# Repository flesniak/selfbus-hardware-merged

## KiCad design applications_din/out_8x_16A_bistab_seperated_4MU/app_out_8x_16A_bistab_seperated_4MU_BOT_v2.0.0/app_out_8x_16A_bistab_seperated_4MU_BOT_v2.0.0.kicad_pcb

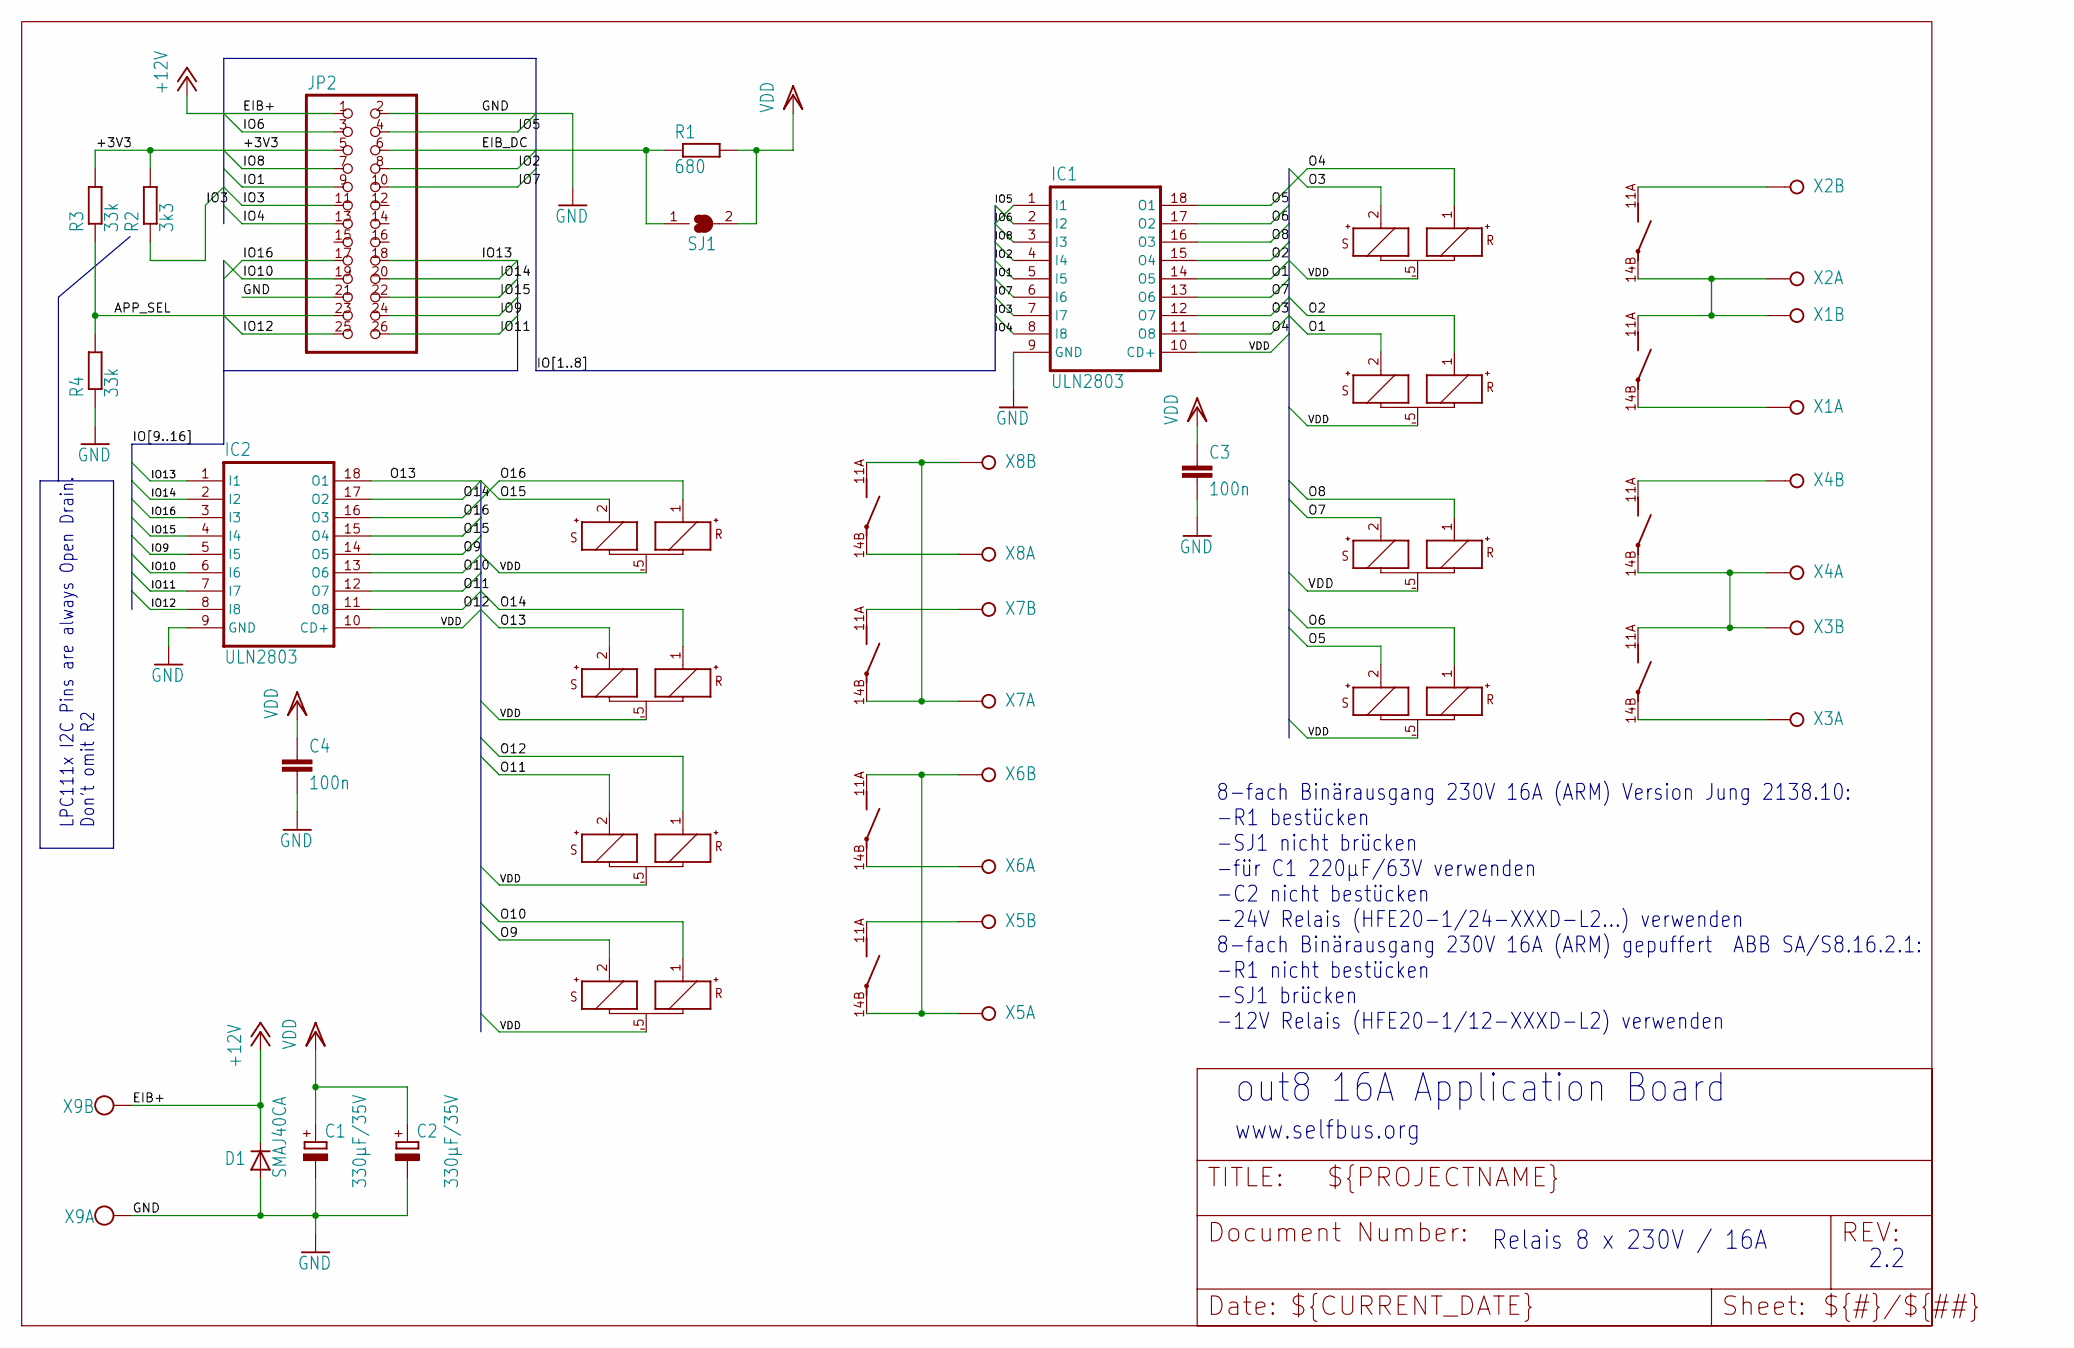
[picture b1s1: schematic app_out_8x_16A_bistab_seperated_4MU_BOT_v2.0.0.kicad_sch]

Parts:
C1, C2: 330µF/35V; E3,5-8
C3, C4: 100n; C1206
D1: SMAJ40CA; SMB
IC1, IC2: ULN2803; SO18W
JP2: A; 2X13SMD
K1, K2, K3, K4, K5, K6, K7, K8: HFE20-1-024-1HD504; HFE20-3-504
R1: 680; M1206
R2: 3k3; M1206
R3, R4: 33k; M1206
SJ1: A; SolderJumper-2_P1.3mm_Open_Pad1.0x1.5mm
X1, X2, X3, X4, X5, X6, X7, X8: W237-02P; W237-132
X9: W237-102; W237-132

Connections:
+12V: D1.1 (C), JP2.1, X9.2 (KL)
/+3V3: JP2.5, R2.2, R3.2
/APP_SEL: JP2.23, R3.1, R4.2
/EIB_DC: JP2.6, R1.1, SJ1.1
/IO1: IC1.5 (I5), JP2.9
/IO2: IC1.4 (I4), JP2.8
/IO3: IC1.7 (I7), JP2.11, R2.1
/IO4: IC1.8 (I8), JP2.13
/IO5: IC1.1 (I1), JP2.4
/IO6: IC1.2 (I2), JP2.3
/IO7: IC1.6 (I6), JP2.10
/IO8: IC1.3 (I3), JP2.7
/IO9: IC2.5 (I5), JP2.24
/IO10: IC2.6 (I6), JP2.19
/IO11: IC2.7 (I7), JP2.26
/IO12: IC2.8 (I8), JP2.25
/IO13: IC2.1 (I1), JP2.18
/IO14: IC2.2 (I2), JP2.20
/IO15: IC2.4 (I4), JP2.22
/IO16: IC2.3 (I3), JP2.17
/O1: IC1.14 (O5), K1.2 (S+)
/O2: IC1.15 (O4), K1.1 (R+)
/O3: IC1.12 (O7), K2.2 (S+)
/O4: IC1.11 (O8), K2.1 (R+)
/O5: IC1.18 (O1), K3.2 (S+)
/O6: IC1.17 (O2), K3.1 (R+)
/O7: IC1.13 (O6), K4.2 (S+)
/O8: IC1.16 (O3), K4.1 (R+)
/O9: IC2.14 (O5), K5.2 (S+)
/O10: IC2.13 (O6), K5.1 (R+)
/O11: IC2.12 (O7), K6.2 (S+)
/O12: IC2.11 (O8), K6.1 (R+)
/O13: IC2.18 (O1), K7.2 (S+)
/O14: IC2.17 (O2), K7.1 (R+)
/O15: IC2.15 (O4), K8.2 (S+)
/O16: IC2.16 (O3), K8.1 (R+)
GND: C1.-, C2.-, C3.2, C4.2, D1.2 (A), IC1.9 (GND), IC2.9 (GND), JP2.2, JP2.21, R4.1, X9.1 (KL)
unnamed: K1.14B (PA), X1.1 (KL)
unnamed: K1.11A (PB), K2.14B (PA), X1.2 (KL), X2.1 (KL)
unnamed: K2.11A (PB), X2.2 (KL)
unnamed: K3.14B (PA), X3.1 (KL)
unnamed: K3.11A (PB), K4.14B (PA), X3.2 (KL), X4.1 (KL)
unnamed: K4.11A (PB), X4.2 (KL)
unnamed: K5.14B (PA), K6.11A (PB), X5.1 (KL), X6.2 (KL)
unnamed: K5.11A (PB), X5.2 (KL)
unnamed: K6.14B (PA), X6.1 (KL)
unnamed: K7.14B (PA), K8.11A (PB), X7.1 (KL), X8.2 (KL)
unnamed: K7.11A (PB), X7.2 (KL)
unnamed: K8.14B (PA), X8.1 (KL)
VDD: C1.+, C2.+, C3.1, C4.1, IC1.10 (CD+), IC2.10 (CD+), K1.5 (-), K2.5 (-), K3.5 (-), K4.5 (-), K5.5 (-), K6.5 (-), K7.5 (-), K8.5 (-), R1.2, SJ1.2

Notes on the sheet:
www.selfbus.org
out8 16A Application Board
2.2
8-fach Binärausgang 230V 16A (ARM) Version Jung 2138.10: -R1 bestücken -SJ1 nicht brücken -für C1 220µF/63V verwenden -C2 nicht bestücken -24V Relais (HFE20-1/24-XXXD-L2...) verwenden 8-fach Binärausgang 230V 16A (ARM) gepuffert ABB SA/S8.16.2.1: -R1 nicht bestücken -SJ1 brücken -12V Relais (HFE20-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
Relais 8 x 230V / 16A
LPC111x I2C Pins are always Open Drain. Don't omit R2~{}

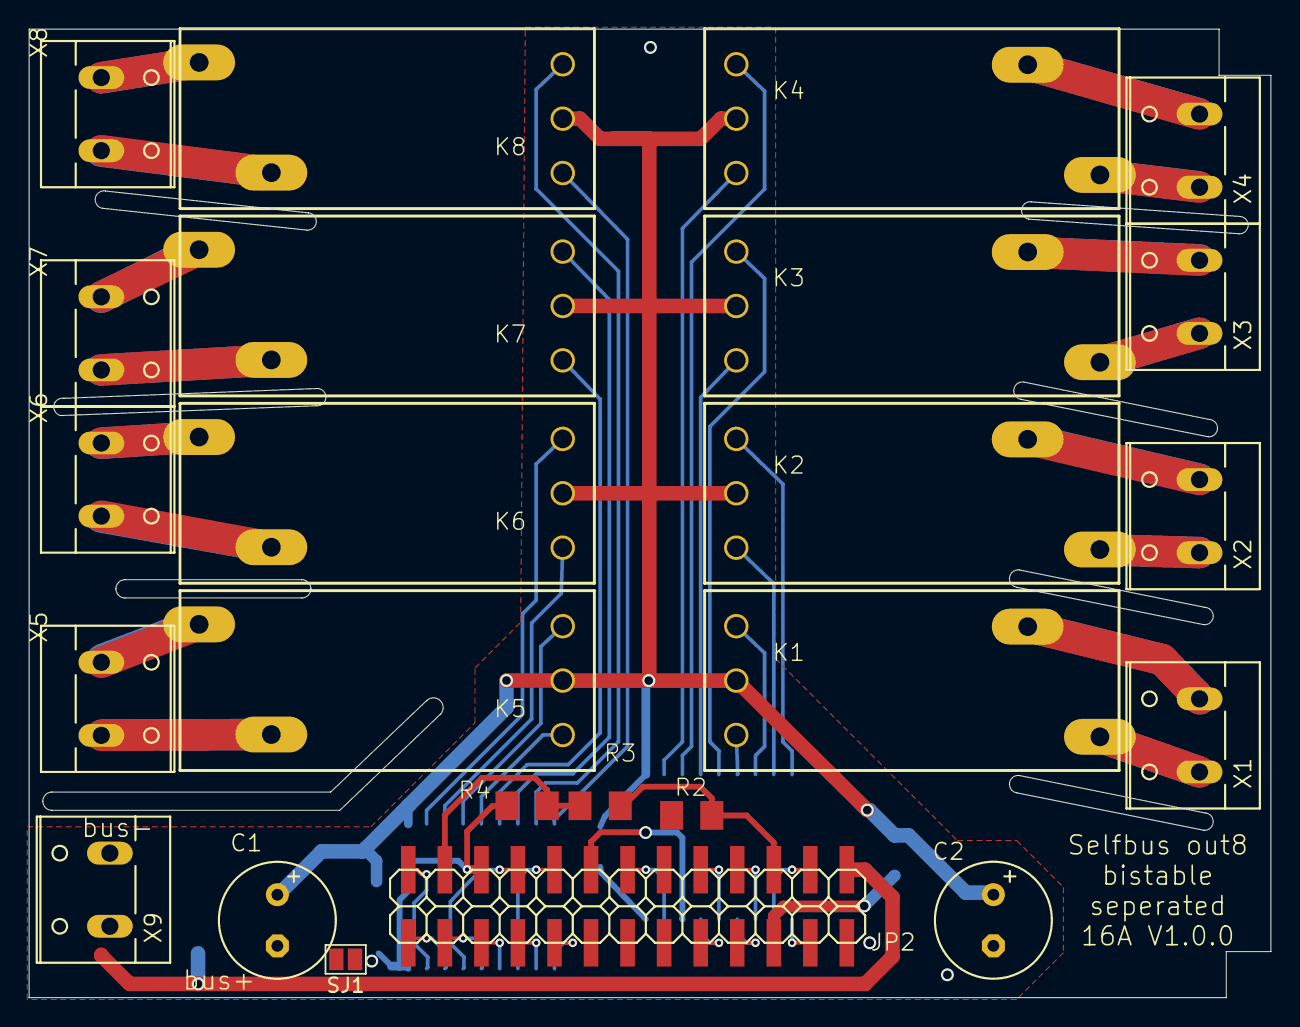
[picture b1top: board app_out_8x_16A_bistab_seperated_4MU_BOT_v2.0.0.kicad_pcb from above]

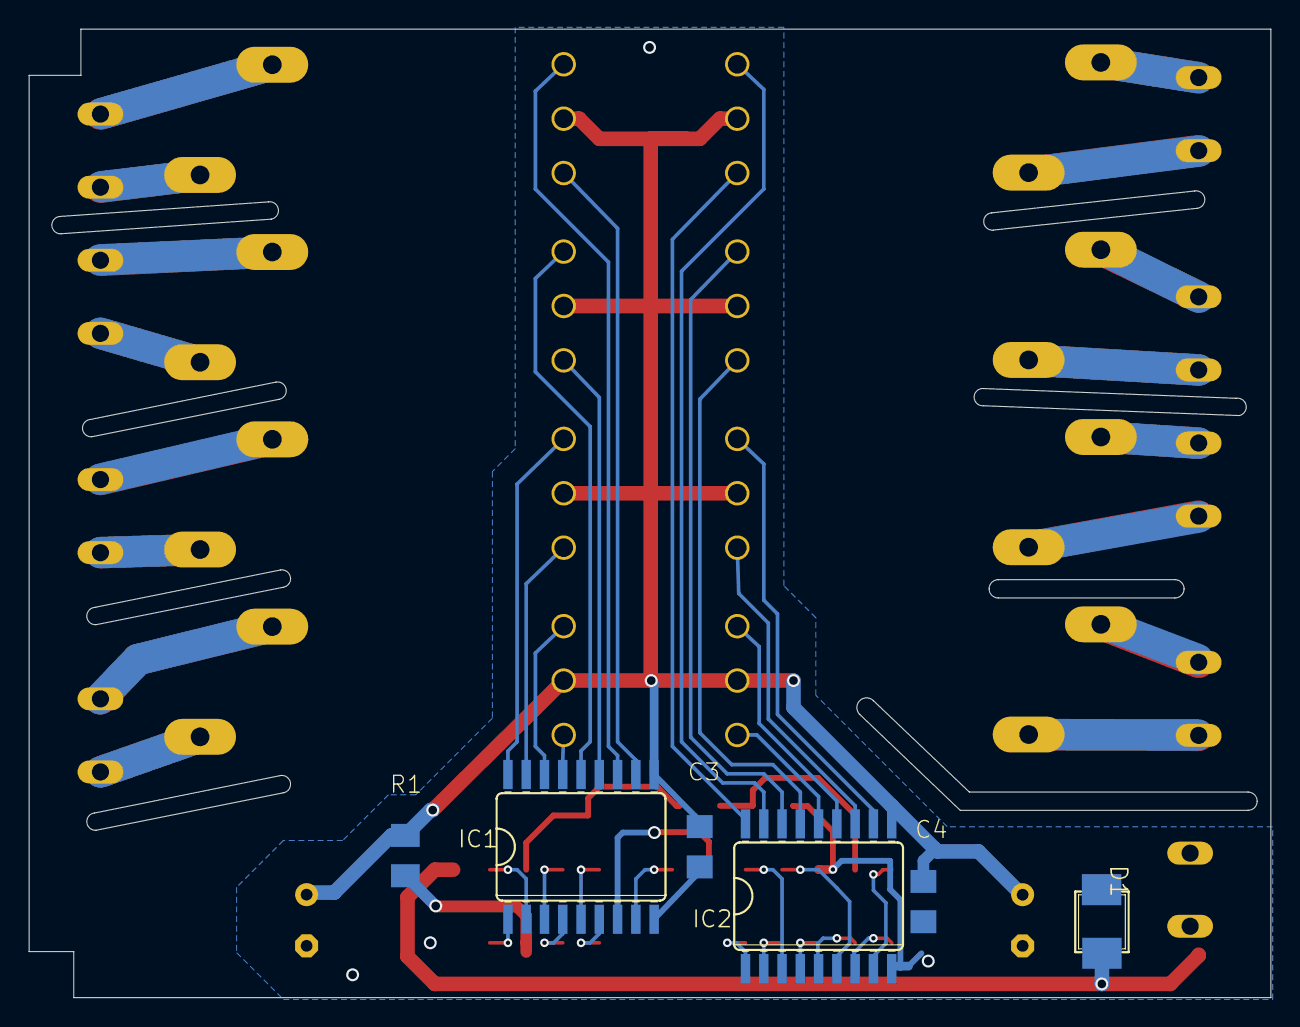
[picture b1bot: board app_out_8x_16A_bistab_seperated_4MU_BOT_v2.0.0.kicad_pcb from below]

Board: 2 copper layers, 86.3 x 67.3 mm, 30 parts (6 on the bottom side), 50 nets.

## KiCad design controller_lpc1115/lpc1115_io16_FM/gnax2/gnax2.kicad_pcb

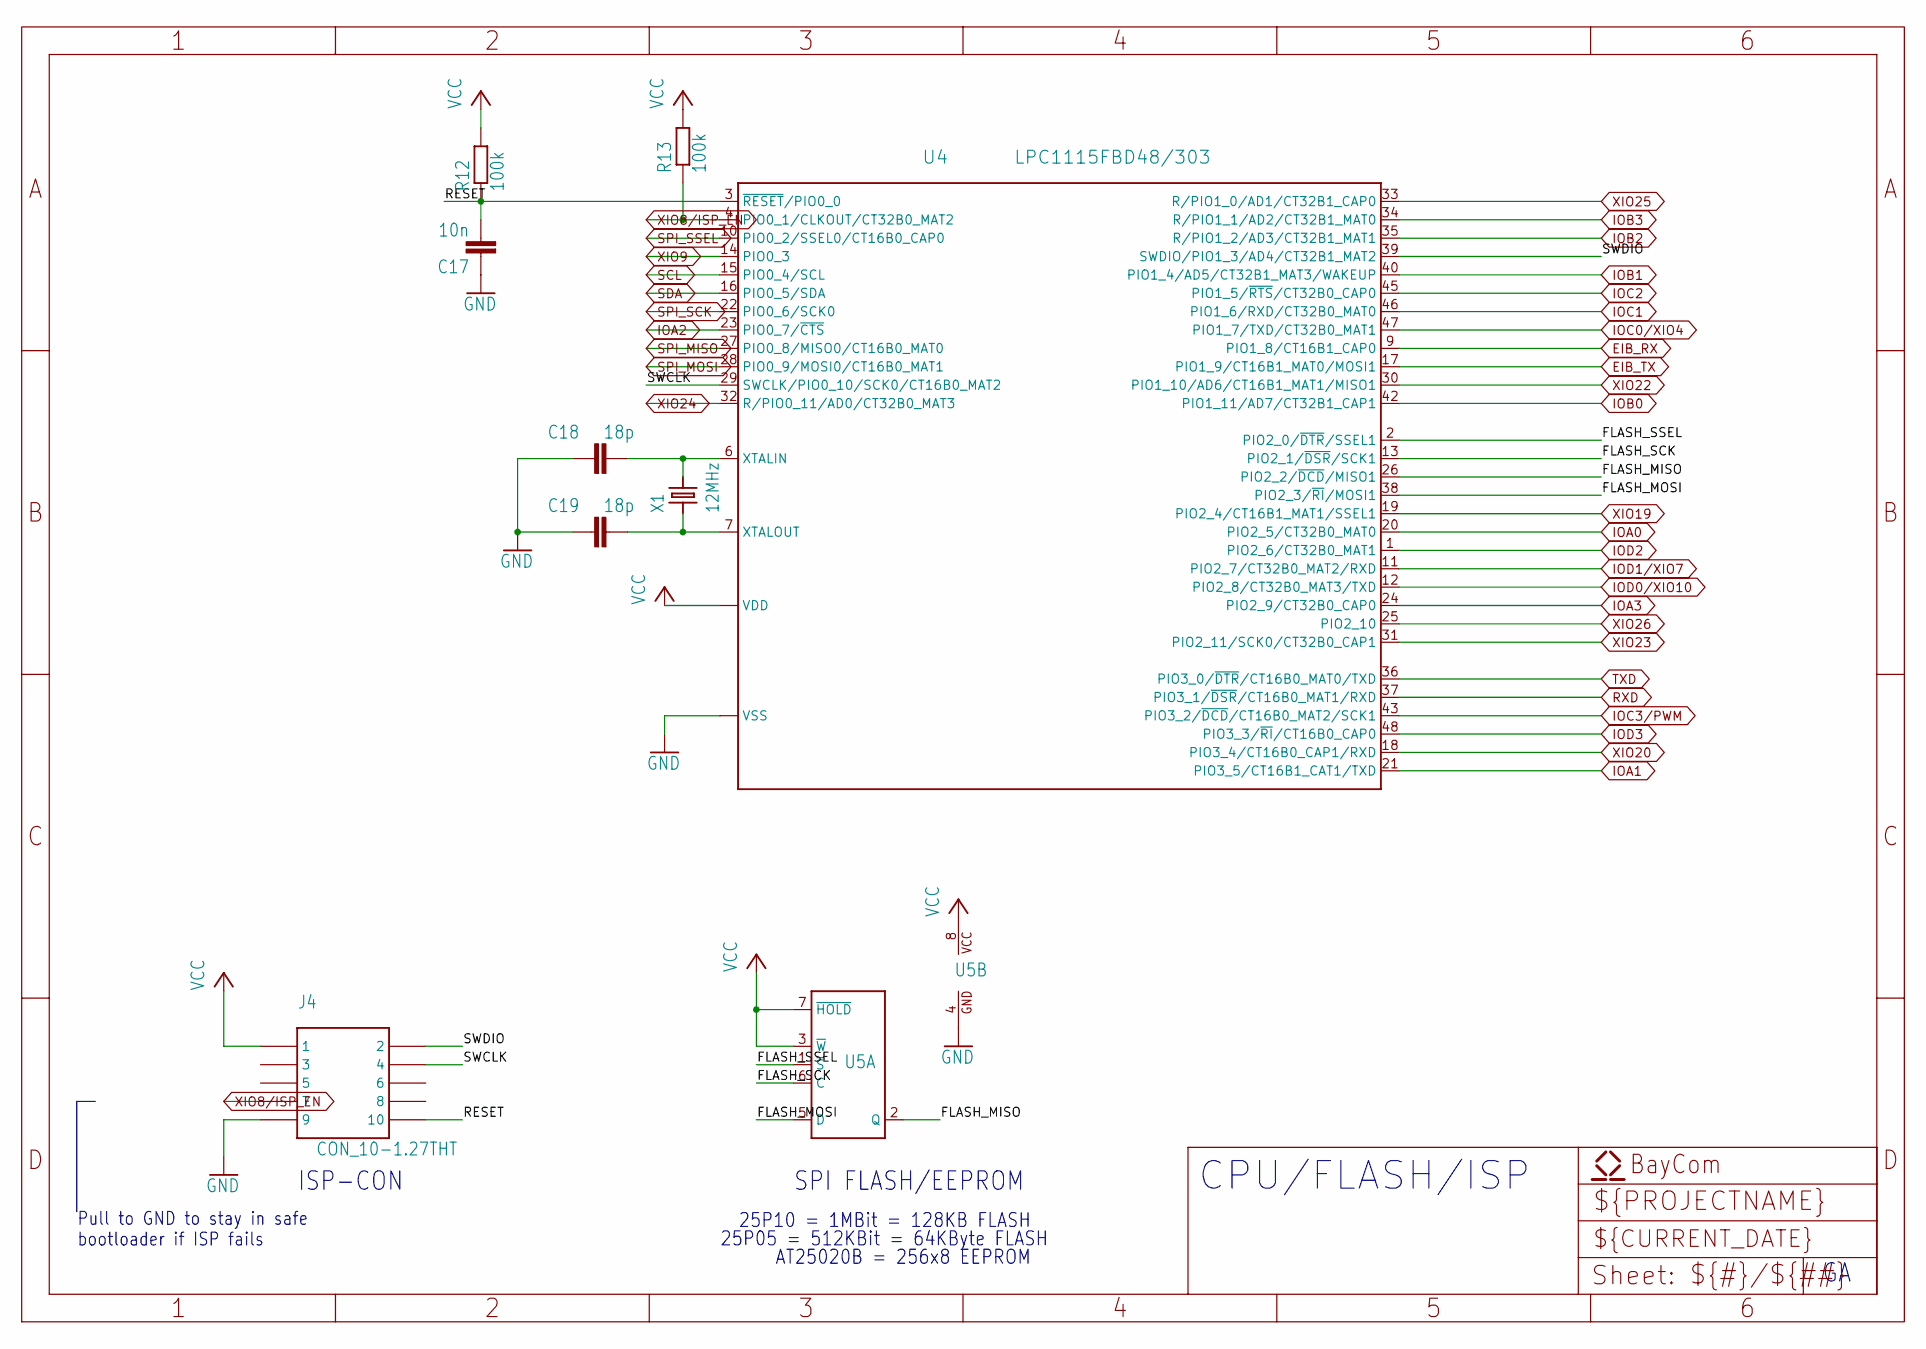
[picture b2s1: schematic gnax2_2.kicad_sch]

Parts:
C17: 10n; C0603K
C18, C19: 18p; C0603K
J4: CON_10-1.27THT; CON2X5_127-THT
R12, R13: 100k; R0603
U4: LPC1115FBD48/303; SOT313-2
U5: ST95P08M; SO08
X1: 12MHz; XTAL_5X3.2

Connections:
EIB_RX: U4.9 (PIO1_8/CT16B1_CAP0); also elsewhere on the board
EIB_TX: U4.17 (PIO1_9/CT16B1_MAT0/MOSI1); also elsewhere on the board
FLASH_MISO: U4.26 (PIO2_2/~DCD/MISO1), U5.2 (Q)
FLASH_MOSI: U4.38 (PIO2_3/~RI/MOSI1), U5.5 (D)
FLASH_SCK: U4.13 (PIO2_1/~DSR/SCK1), U5.6 (C)
FLASH_SSEL: U4.2 (PIO2_0/~DTR/SSEL1), U5.1 (~S)
GND: C17.1, C18.1, C19.1, J4.9, U4.5 (VSS), U4.41 (VSS), U5.4 (GND); also elsewhere on the board
IOA0: U4.20 (PIO2_5/CT32B0_MAT0); also elsewhere on the board
IOA1: U4.21 (PIO3_5/CT16B1_CAT1/TXD); also elsewhere on the board
IOA2: U4.23 (PIO0_7/~CTS); also elsewhere on the board
IOA3: U4.24 (PIO2_9/CT32B0_CAP0); also elsewhere on the board
IOB0: U4.42 (PIO1_11/AD7/CT32B1_CAP1); also elsewhere on the board
IOB1: U4.40 (PIO1_4/AD5/CT32B1_MAT3/WAKEUP); also elsewhere on the board
IOB2: U4.35 (R/PIO1_2/AD3/CT32B1_MAT1); also elsewhere on the board
IOB3: U4.34 (R/PIO1_1/AD2/CT32B1_MAT0); also elsewhere on the board
IOC0/XIO4: U4.47 (PIO1_7/TXD/CT32B0_MAT1); also elsewhere on the board
IOC1: U4.46 (PIO1_6/RXD/CT32B0_MAT0); also elsewhere on the board
IOC2: U4.45 (PIO1_5/~RTS/CT32B0_CAP0); also elsewhere on the board
IOC3/PWM: U4.43 (PIO3_2/~DCD/CT16B0_MAT2/SCK1); also elsewhere on the board
IOD0/XIO10: U4.12 (PIO2_8/CT32B0_MAT3/TXD); also elsewhere on the board
IOD1/XIO7: U4.11 (PIO2_7/CT32B0_MAT2/RXD); also elsewhere on the board
IOD2: U4.1 (PIO2_6/CT32B0_MAT1); also elsewhere on the board
IOD3: U4.48 (PIO3_3/~RI/CT16B0_CAP0); also elsewhere on the board
unnamed: C19.2, U4.7 (XTALOUT), X1.1
unnamed: C18.2, U4.6 (XTALIN), X1.2
RESET: C17.2, J4.10, R12.1, U4.3 (~RESET/PIO0_0)
RXD: U4.37 (PIO3_1/~DSR/CT16B0_MAT1/RXD); also elsewhere on the board
SCL: U4.15 (PIO0_4/SCL); also elsewhere on the board
SDA: U4.16 (PIO0_5/SDA); also elsewhere on the board
SPI_MISO: U4.27 (PIO0_8/MISO0/CT16B0_MAT0); also elsewhere on the board
SPI_MOSI: U4.28 (PIO0_9/MOSI0/CT16B0_MAT1); also elsewhere on the board
SPI_SCK: U4.22 (PIO0_6/SCK0); also elsewhere on the board
SPI_SSEL: U4.10 (PIO0_2/SSEL0/CT16B0_CAP0); also elsewhere on the board
SWCLK: J4.4, U4.29 (SWCLK/PIO0_10/SCK0/CT16B0_MAT2)
SWDIO: J4.2, U4.39 (SWDIO/PIO1_3/AD4/CT32B1_MAT2)
TXD: U4.36 (PIO3_0/~DTR/CT16B0_MAT0/TXD); also elsewhere on the board
XIO8/ISP_EN: J4.7, R13.1, U4.4 (PIO0_1/CLKOUT/CT32B0_MAT2); also elsewhere on the board
XIO9: U4.14 (PIO0_3); also elsewhere on the board
XIO19: U4.19 (PIO2_4/CT16B1_MAT1/SSEL1); also elsewhere on the board
XIO20: U4.18 (PIO3_4/CT16B0_CAP1/RXD); also elsewhere on the board
XIO22: U4.30 (PIO1_10/AD6/CT16B1_MAT1/MISO1); also elsewhere on the board
XIO23: U4.31 (PIO2_11/SCK0/CT32B0_CAP1); also elsewhere on the board
XIO24: U4.32 (R/PIO0_11/AD0/CT32B0_MAT3); also elsewhere on the board
XIO25: U4.33 (R/PIO1_0/AD1/CT32B1_CAP0); also elsewhere on the board
XIO26: U4.25 (PIO2_10); also elsewhere on the board

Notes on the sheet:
25P10 = 1MBit = 128KB FLASH
25P05 = 512KBit = 64KByte FLASH
ISP-CON
CPU/FLASH/ISP
AT25020B = 256x8 EEPROM
SPI FLASH/EEPROM
Pull to GND to stay in safe bootloader if ISP fails

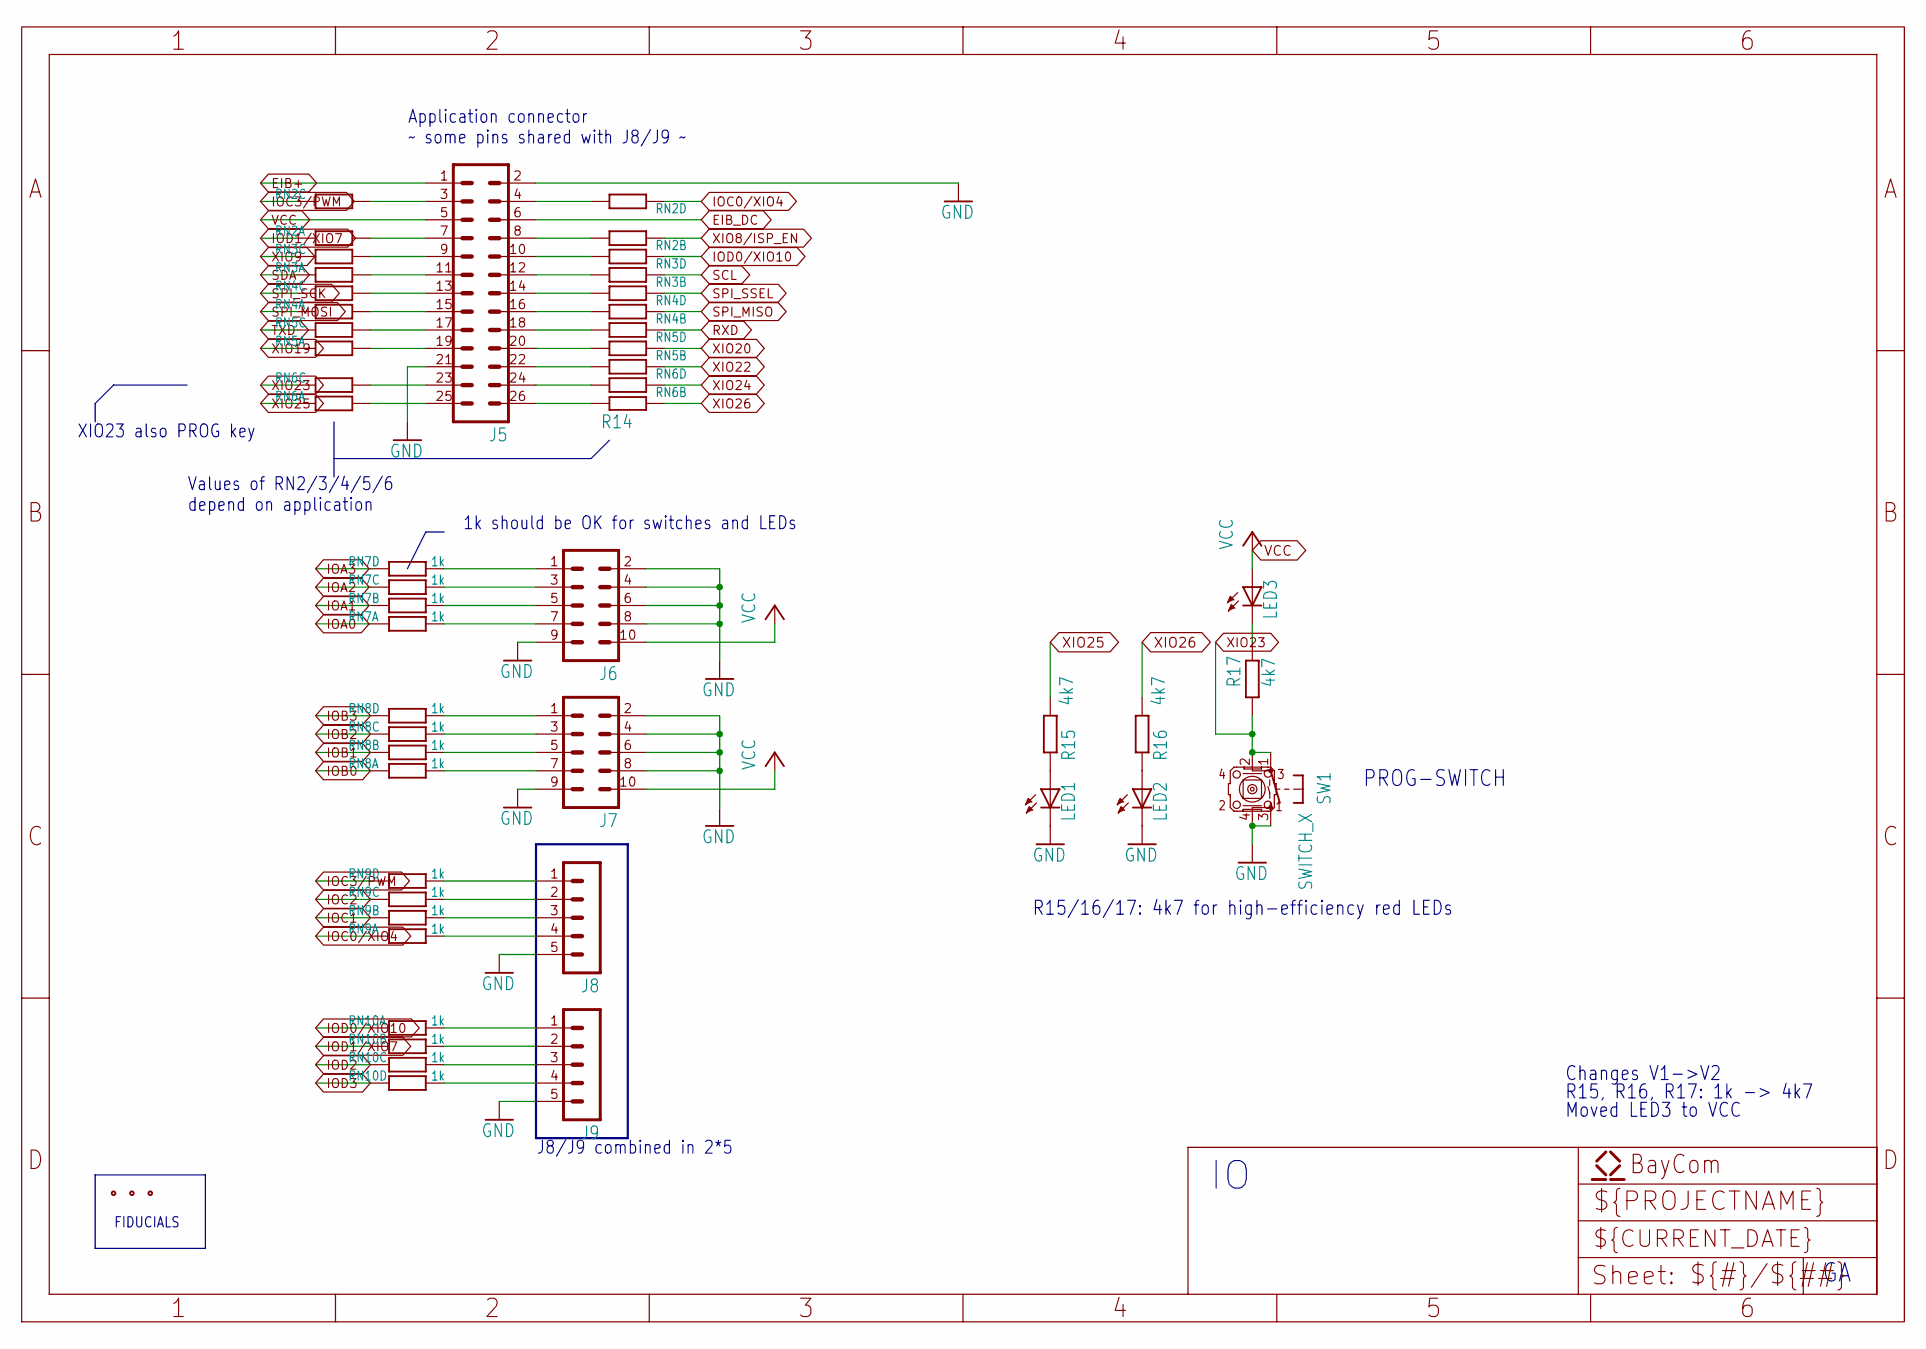
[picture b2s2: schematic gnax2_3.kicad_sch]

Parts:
J5: MA13-2
J6, J7: MA05-2
J8, J9: MA05-1
LED1, LED2, LED3: LEDCHIP-LED0805; CHIP-LED0805
R14: R-EU_R0603; R0603
R15, R16, R17: 4k7; R0603
RN2, RN3, RN4, RN5, RN6: RNET12061; 1206_8
RN7, RN8, RN9, RN10: 1k; 1206_8
SW1: SWITCH_X; SWITCH_PTS810
X3, X8, X9: FIDUCIAL_0.6-1.2MM; FIDUCIAL0.6-1.2

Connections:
EIB+: J5.1; also elsewhere on the board
EIB_DC: J5.6; also elsewhere on the board
GND: J5.2, J5.21, J6.2, J6.4, J6.6, J6.8, J6.9, J7.2, J7.4, J7.6, J7.8, J7.9, J8.5, J9.5, LED1.C, LED2.C, SW1.3 (S), SW1.4 (S1); also elsewhere on the board
IOA0: RN7.1; also elsewhere on the board
IOA1: RN7.2; also elsewhere on the board
IOA2: RN7.3; also elsewhere on the board
IOA3: RN7.4; also elsewhere on the board
IOB0: RN8.1; also elsewhere on the board
IOB1: RN8.2; also elsewhere on the board
IOB2: RN8.3; also elsewhere on the board
IOB3: RN8.4; also elsewhere on the board
IOC0/XIO4: RN2.4, RN9.1; also elsewhere on the board
IOC1: RN9.2; also elsewhere on the board
IOC2: RN9.3; also elsewhere on the board
IOC3/PWM: RN2.3, RN9.4; also elsewhere on the board
IOD0/XIO10: RN3.4, RN10.1; also elsewhere on the board
IOD1/XIO7: RN2.1, RN10.2; also elsewhere on the board
IOD2: RN10.3; also elsewhere on the board
IOD3: RN10.4; also elsewhere on the board
unnamed: J6.7, RN7.8
unnamed: LED1.A, R15.1
unnamed: J6.5, RN7.7
unnamed: J6.3, RN7.6
unnamed: J6.1, RN7.5
unnamed: J7.5, RN8.7
unnamed: J7.3, RN8.6
unnamed: J7.7, RN8.8
unnamed: J7.1, RN8.5
unnamed: LED3.C, R17.2
unnamed: J8.3, RN9.7
unnamed: J8.2, RN9.6
unnamed: J8.4, RN9.8
unnamed: J9.1, RN10.8
unnamed: J9.2, RN10.7
unnamed: J9.3, RN10.6
unnamed: J9.4, RN10.5
unnamed: J8.1, RN9.5
unnamed: LED2.A, R16.1
unnamed: J5.3, RN2.6
unnamed: J5.7, RN2.8
unnamed: J5.9, RN3.6
unnamed: J5.11, RN3.8
unnamed: J5.13, RN4.6
unnamed: J5.4, RN2.5
unnamed: J5.8, RN2.7
unnamed: J5.10, RN3.5
unnamed: J5.12, RN3.7
unnamed: J5.14, RN4.5
unnamed: J5.15, RN4.8
unnamed: J5.17, RN5.6
unnamed: J5.16, RN4.7
unnamed: J5.18, RN5.5
unnamed: J5.19, RN5.8
unnamed: J5.20, RN5.7
unnamed: J5.22, RN6.5
unnamed: J5.23, RN6.6
unnamed: J5.24, RN6.7
unnamed: J5.25, RN6.8
unnamed: J5.26, R14.1
RXD: RN5.4; also elsewhere on the board
SCL: RN3.2; also elsewhere on the board
SDA: RN3.1; also elsewhere on the board
SPI_MISO: RN4.2; also elsewhere on the board
SPI_MOSI: RN4.1; also elsewhere on the board
SPI_SCK: RN4.3; also elsewhere on the board
SPI_SSEL: RN4.4; also elsewhere on the board
TXD: RN5.3; also elsewhere on the board
XIO8/ISP_EN: RN2.2; also elsewhere on the board
XIO9: RN3.3; also elsewhere on the board
XIO19: RN5.1; also elsewhere on the board
XIO20: RN5.2; also elsewhere on the board
XIO22: RN6.4; also elsewhere on the board
XIO23: R17.1, RN6.3, SW1.1, SW1.2 (P1); also elsewhere on the board
XIO24: RN6.2; also elsewhere on the board
XIO25: R15.2, RN6.1; also elsewhere on the board
XIO26: R14.2, R16.2; also elsewhere on the board

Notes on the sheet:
XIO23 also PROG key~{}
Moved LED3 to VCC
1k should be OK for switches and LEDs
FIDUCIALS
R15/16/17: 4k7 for high-efficiency red LEDs
Changes V1->V2
J8/J9 combined in 2*5
Application connector ~~{} some pins shared with J8/J9 ~~{}
R15, R16, R17: 1k -> 4k7
PROG-SWITCH
Values of RN2/3/4/5/6 depend on application

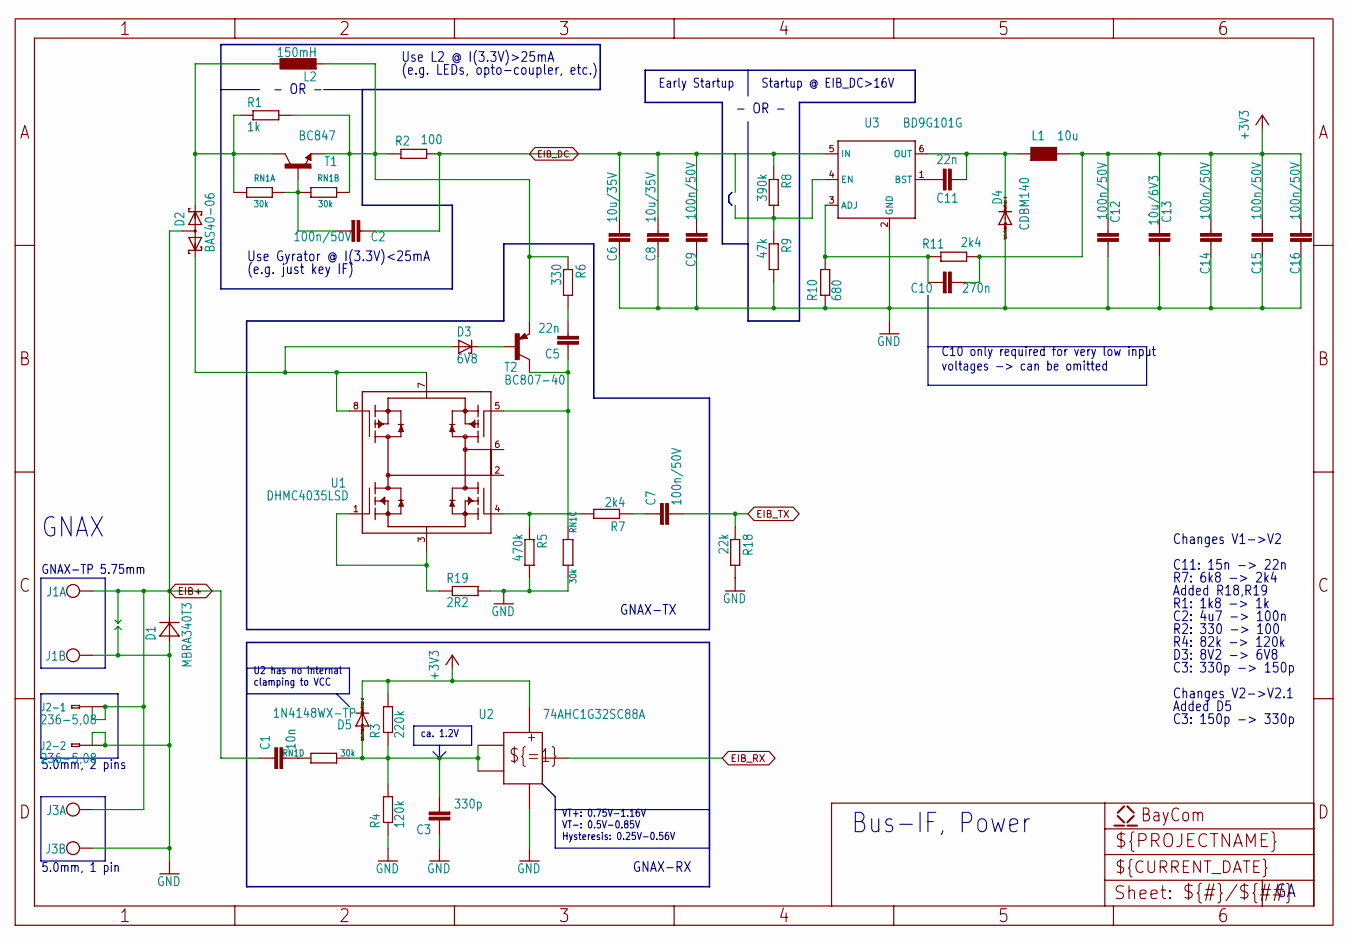
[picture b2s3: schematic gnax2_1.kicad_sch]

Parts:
C1: 10n; C0603K
C2, C7, C9, C12, C14, C15, C16: 100n/50V; C0603K
C3: 330p; C0603K
C5, C11: 22n; C0603K
C6, C8: 10u/35V; C1206K
C10: 270n; C0603K
C13: 10u/6V3; C0603K
D1: MBRA340T3; SMA
D2: BAS40-06; SOT23
D3: 6V8; SOT23
D4: CDBM140; SOD123
D5: 1N4148WX-TP; SOD323-R
J1: CON_2KNX; KNX2
J2-1, J2-2: 236-5,08; 236-4XX
J3: CON_2; W237-102
L1: 10u; L_ELL3
L2: 150mH; 0204_5
R1: 1k; R0603
R2: 100; R0603
R3: 220k; R0603
R4: 120k; R0603
R5: 470k; R0603
R6: 330; R0603
R7, R11: 2k4; R0603
R8: 390k; R0603
R9: 47k; R0603
R10: 680; R0603
R18: 22k; R0603
R19: 2R2; R0805
RN1: 30k; 1206_8
T1: BC847; SOT23
T2: BC807-40; SOT23-BEC
U1: DHMC4035LSD; SOP8
U2: 74AHC1G32SC88A; SC88A
U3: BD9G101G; SOT23-6

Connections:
EIB+: C1.1, D1.C, D2.3 (AA), J1.1, J2-1.1@1 (A1), J2-1.1@2 (B1), J3.1; also elsewhere on the board
EIB_DC: C2.1, C6.1, C8.1, C9.2, R2.2, R8.1, U3.5 (IN); also elsewhere on the board
EIB_RX: U2.4 (Y); also elsewhere on the board
EIB_TX: C7.2, R18.1; also elsewhere on the board
FX: R19.1, U1.1 (N1G), U1.3 (N1S/N2S)
GND: C3.1, C6.2, C8.2, C9.1, C12.1, C13.1, C14.1, C15.1, C16.1, D1.A, D4.A, J1.2, J2-2.1@1 (A1), J2-2.1@2 (B1), J3.2, R4.1, R5.2, R9.2, R10.1, R18.2, R19.2, RN1.6, U2.3 (GND), U3.2 (GND); also elsewhere on the board
LX: C11.1, D4.C, L1.P$1, U3.6 (OUT)
unnamed: D2.1 (K1), D3.1 (A), U1.7 (P1S/P2S), U1.8 (P1G)
unnamed: C1.2, RN1.4
unnamed: R5.1, R7.2, U1.4 (N2G)
unnamed: C7.1, R7.1
unnamed: D2.2 (K2), L2.1, R1.1, RN1.1, T1.3 (C)
unnamed: C5.1, RN1.3, T2.C, U1.5 (P2G)
unnamed: C3.2, D5.A, R3.1, R4.2, RN1.5, U2.1 (A), U2.2 (B)
unnamed: C5.2, R6.2
unnamed: C11.2, U3.1 (BST)
unnamed: R8.2, R9.1, U3.4 (EN)
unnamed: C10.1, R10.2, R11.1, U3.3 (ADJ)
unnamed: C2.2, RN1.7, RN1.8, T1.1 (B)
unnamed: D3.3 (C), T2.B
unnamed: L2.2, R1.2, R2.1, R6.1, RN1.2, T1.2 (E), T2.E

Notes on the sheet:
Use L2 @ I(3.3V)>25mA
Changes V2->V2.1
D3: 8V2 -> 6V8
C3: 330p -> 150p
C11: 15n -> 22n
GNAX
(e.g. LEDs, opto-coupler, etc.)
C2: 4u7 -> 100n
C10 only required for very low input voltages -> can be omitted
GNAX-TX
(e.g. just key IF)
R4: 82k -> 120k
- OR -
C3: 150p -> 330p
U2 has no internal clamping to VCC~{}
Added R18,R19
Early Startup
Startup @ EIB_DC>16V
ca. 1.2V
R2: 330 -> 100
Use Gyrator @ I(3.3V)<25mA
5.0mm, 1 pin
GNAX-TP 5.75mm
Changes V1->V2
R7: 6k8 -> 2k4
GNAX-RX
VT+: 0.75V-1.16V VT-: 0.5V-0.85V Hysteresis: 0.25V-0.56V
Added D5
Bus-IF, Power
R1: 1k8 -> 1k
5.0mm, 2 pins

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
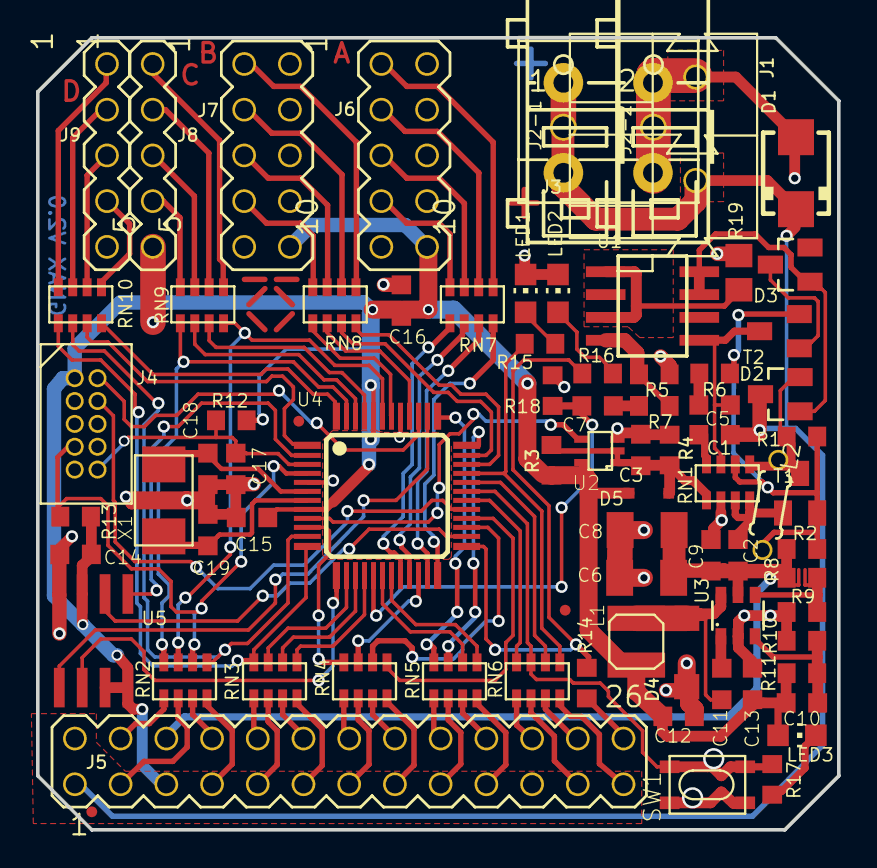
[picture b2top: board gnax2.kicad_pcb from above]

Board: 4 copper layers, 44.5 x 44.0 mm, 80 parts (0 on the bottom side), 104 nets.

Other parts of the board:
U$1: BAYCOM_LOGO
